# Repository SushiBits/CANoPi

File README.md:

# SushiBits CANoPI

Isolated CAN or Raspberry Pi Zero

## Introduction & Goal

I have finally got around to take a jab at the CAN bus. This interface board
allows the CAN interface to be used by the Raspberry Pi Zero. It also provides
galvanic isolation for the CAN interface for added safety.

It also includes a real time clock for the Pi, as automated controllers often
calls for one.

## License

This is [open source hardware](http://www.oshwa.org/), licensed under the
[3-clause BSD license](LICENSE.md).

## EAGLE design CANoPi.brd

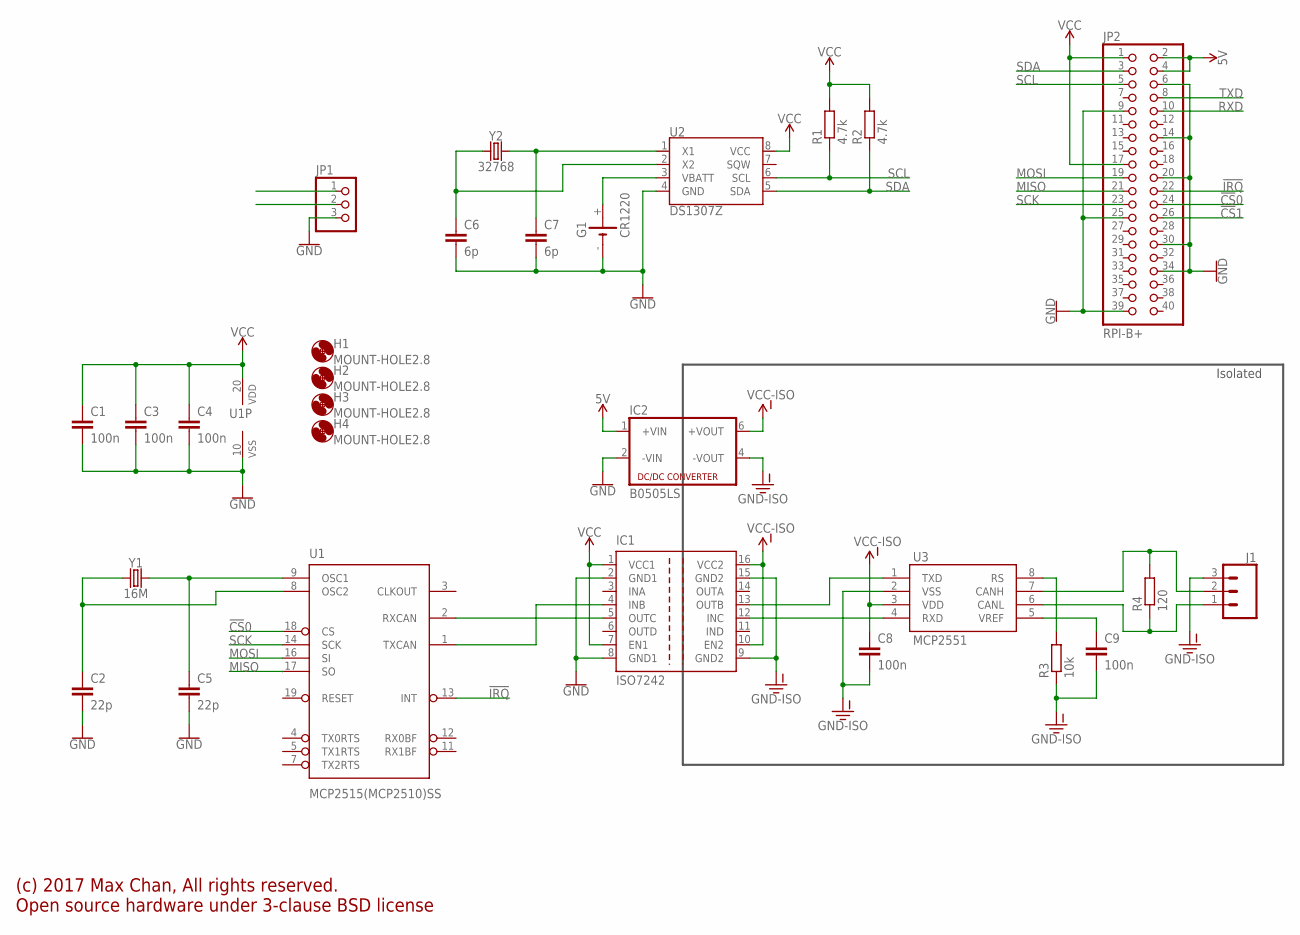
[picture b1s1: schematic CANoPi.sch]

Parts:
C1, C3, C4, C8, C9: 100n; C0603
C2, C5: 22p; C0603
C6, C7: 6p; C0603
G1: CR1220; CH291-1220LF
H1, H2, H3, H4: MOUNT-HOLE2.8; 2,8
IC1: ISO7242; SO-16DW
IC2: B0505LS; NMA-SINGLE
J1: CONN_03SCREW; SCREWTERMINAL-3.5MM-3
JP1: PINHD-1X3/90; 1X03/90
JP2: RPI-B+; 2X20
R1, R2: 4.7k; R0603
R3: 10k; R0603
R4: 120; R0603
U1: MCP2515(MCP2510)SS; SSOP20
U2: DS1307Z; SO08-0.15
U3: MCP2551; SO08
Y1: 16M; CRYSTAL-SMD-5X3.2-4PAD
Y2: 32768; CRYSTAL-SMD-3.2X1.5MM

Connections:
5V: IC2.1 (+VIN), JP2.2, JP2.4
!CS!0: JP2.24, U1.18 (CS)
!CS!1: JP2.26
!IRQ: JP2.22, U1.13 (INT)
CANH: J1.2, R4.2, U3.7 (CANH)
CANL: J1.1, R4.1, U3.6 (CANL)
CAN_OSC1: C5.1, U1.9 (OSC1), Y1.3 (2)
CAN_OSC2: C2.1, U1.8 (OSC2), Y1.1
CAN_RS: R3.2, U3.8 (RS)
CAN_VREF: C9.1, U3.5 (VREF)
GND: C1.2, C2.2, C3.2, C4.2, C5.2, C6.2, C7.2, G1.-, IC1.2 (GND1), IC1.8 (GND1), IC2.2 (-VIN), JP1.3, JP2.6, JP2.9, JP2.14, JP2.20, JP2.25, JP2.30, JP2.34, JP2.39, U1.10 (VSS), U2.4 (GND)
GND-ISO: C8.2, C9.2, IC1.9 (GND2), IC1.15 (GND2), IC2.4 (-VOUT), J1.3, R3.1, U3.2 (VSS)
MISO: JP2.21, U1.17 (SO)
MOSI: JP2.19, U1.16 (SI)
RTCX1: C7.1, U2.1 (X1), Y2.P$2 (2)
RTCX2: C6.1, U2.2 (X2), Y2.P$1 (1)
RXCAN: IC1.5 (OUTC), U1.2 (RXCAN)
RXD: JP1.1, JP2.10
RX_CAN: IC1.12 (INC), U3.4 (RXD)
SCK: JP2.23, U1.14 (SCK)
SCL: JP2.5, R1.1, U2.6 (SCL)
SDA: JP2.3, R2.1, U2.5 (SDA)
TXCAN: IC1.4 (INB), U1.1 (TXCAN)
TXD: JP1.2, JP2.8
TX_CAN: IC1.13 (OUTB), U3.1 (TXD)
VBATT: G1.+, U2.3 (VBATT)
VCC: C1.1, C3.1, C4.1, IC1.1 (VCC1), IC1.7 (EN1), JP2.1, JP2.17, R1.2, R2.2, U1.20 (VDD), U2.8 (VCC)
VCC-ISO: C8.1, IC1.10 (EN2), IC1.16 (VCC2), IC2.6 (+VOUT), U3.3 (VDD)

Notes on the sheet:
Isolated
(c) 2017 Max Chan, All rights reserved. Open source hardware under 3-clause BSD license

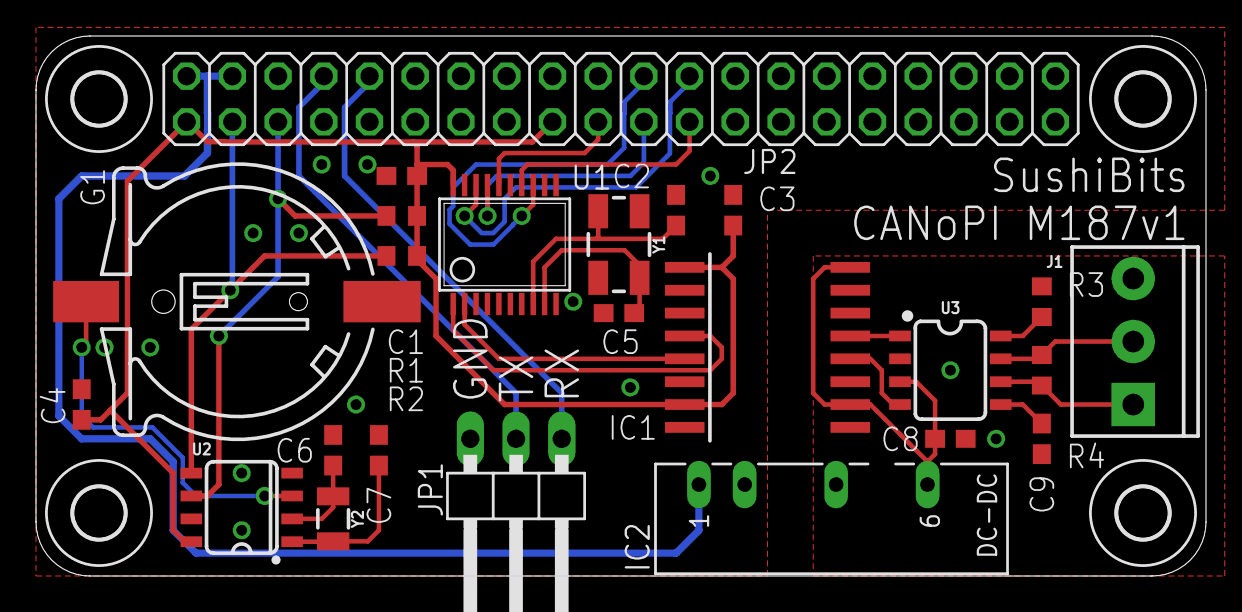
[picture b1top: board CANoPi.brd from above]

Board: 2 copper layers, 65.0 x 30.0 mm, 28 parts (0 on the bottom side), 27 nets.

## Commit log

2017-08-20 Adding files to the project.
2017-08-20 I think it should be safe to include EPF in releases.
2017-08-20 Exclude release files
2017-08-20 Added CANH and CANL markers
2017-08-26 Fixed the CAN GND pin issue

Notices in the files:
parts and their libraries:
SparkFun-Connectors: Licensing: Creative Commons ShareAlike 4.0 International - https://creativecommons.org/licenses/by-sa/4.0
